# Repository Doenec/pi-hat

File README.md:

# pi-hat
collection of different shields to be stacked in raspberry pi

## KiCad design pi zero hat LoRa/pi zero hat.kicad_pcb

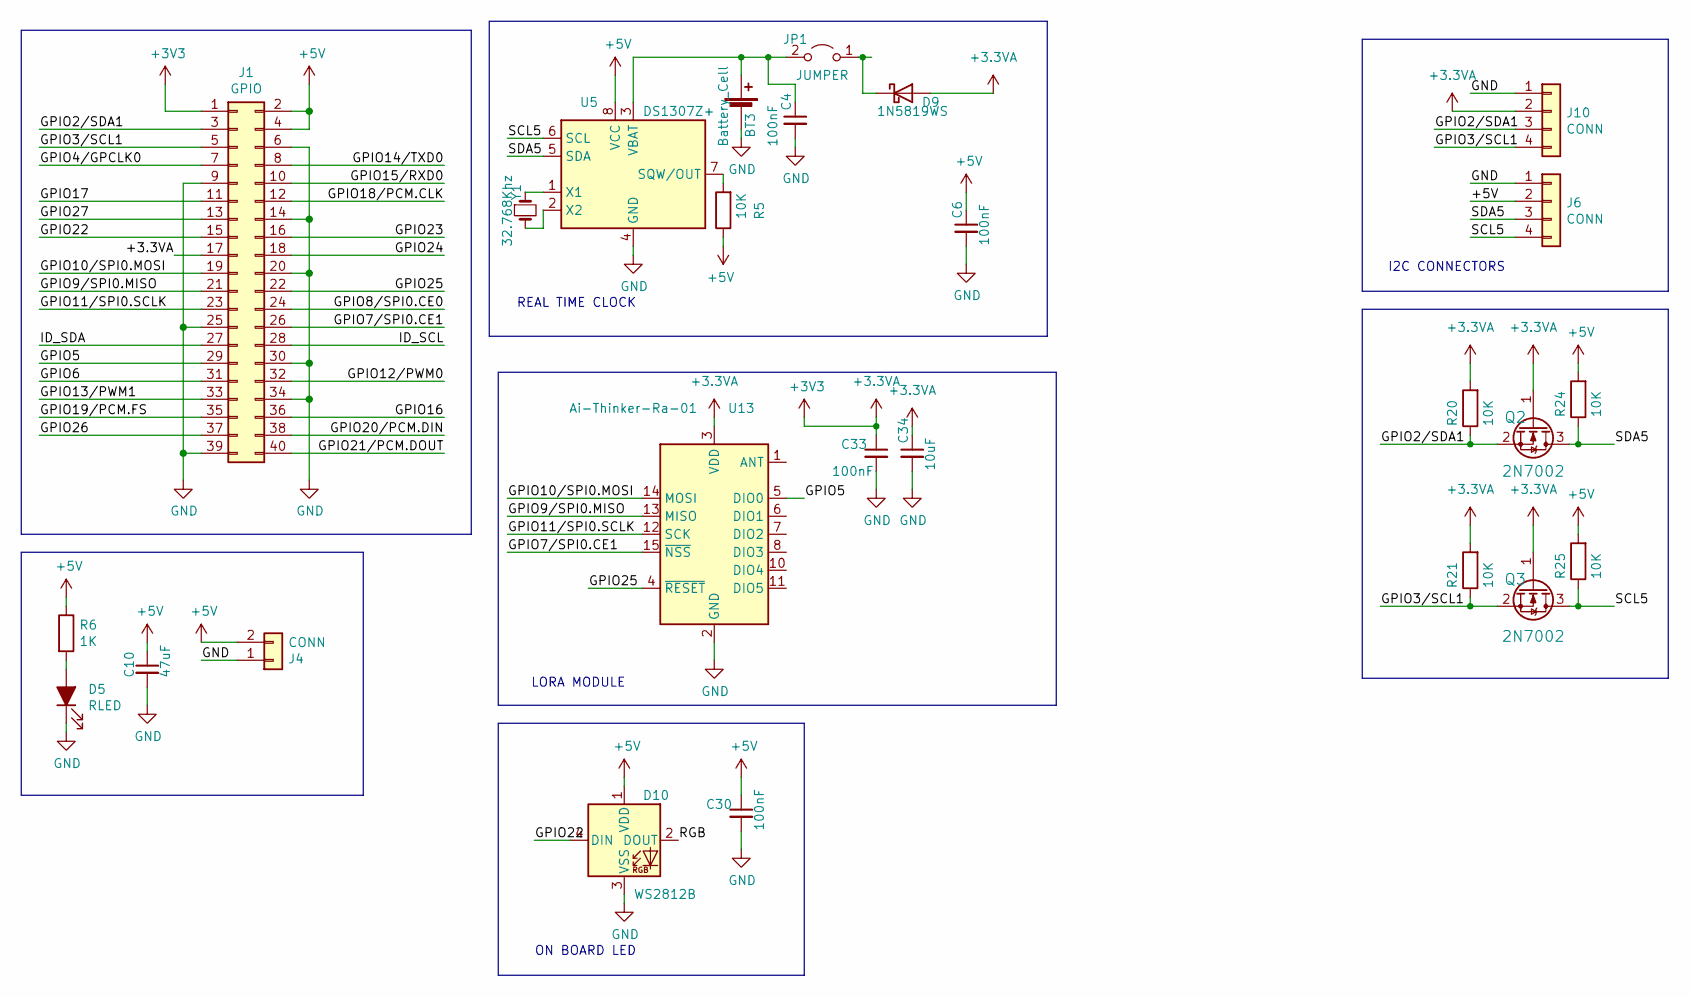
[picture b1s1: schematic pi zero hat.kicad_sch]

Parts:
BT3: Battery_Cell; cr1220-2; MPN CR1220-2; LCSC-PN C70381
C4, C6, C30, C33: 100nF; C_0402_1005Metric; MPN CL05B104KO5NNNC; LCSC-PN C1525
C10: 47uF; C_1206_3216Metric; MPN CL31A476MPHNNNE; LCSC-PN C96123
C34: 10uF; C_0402_1005Metric; MPN CL05A106MQ5NUNC; LCSC-PN C15525
D5: RLED; LED_0603_1608Metric; MPN KT-0603R; LCSC-PN C2286
D9: 1N5819WS; D_SOD-323; MPN 1N5819WS; LCSC-PN C191023
D10: WS2812B; LED_WS2812B_PLCC4_5.0x5.0mm_P3.2mm; MPN WS2812E-V5; LCSC-PN C2920042
J1: GPIO; PinSocket_2x20_P2.54mm_Vertical
J4: CONN; JST_PH_B2B-PH-K_1x02_P2.00mm_Vertical
J6, J10: CONN; PinHeader_1x04_P2.54mm_Vertical
JP1: JUMPER; SolderJumper-2_P1.3mm_Open_RoundedPad1.0x1.5mm
Q2, Q3: 2N7002; SOT-23; MPN 2N7002; LCSC-PN C8545
R5, R20, R21, R24, R25: 10K; R_0402_1005Metric; MPN 0402WGF1002TCE; LCSC-PN C25744
R6: 1K; R_0603_1608Metric; MPN 0603WAF1001T5E; LCSC-PN C21190
U5: DS1307Z+; SOIC-8_3.9x4.9mm_P1.27mm; MPN DS1307Z+T&R; LCSC-PN C9868
U13: Ai-Thinker-Ra-01; Ai-Thinker-Ra-01-LoRa
Y1: 32.768Khz; Crystal_SMD_G8-2Pin_3.2x1.5mm; MPN Q13FC1350000400; LCSC-PN C32346

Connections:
+3.3VA: C33.1, C34.1, D9.2 (A), J1.1, J1.17, J10.2, Q2.1 (G), Q3.1 (G), R20.2, R21.2, U13.3 (VDD)
+5V: C6.1, C10.1, C30.1, D10.1 (VDD), J1.2, J1.4, J4.2, J6.2, R5.1, R6.1, R24.2, R25.2, U5.8 (VCC)
/GPIO2/SDA1: J1.3, J10.3, Q2.2 (S), R20.1
/GPIO3/SCL1: J1.5, J10.4, Q3.2 (S), R21.1
/GPIO4/GPCLK0: J1.7
/GPIO5: J1.29, U13.5 (DIO0)
/GPIO6: J1.31
/GPIO7/SPI0.CE1: J1.26, U13.15 (~NSS)
/GPIO8/SPI0.CE0: J1.24
/GPIO9/SPI0.MISO: J1.21, U13.13 (MISO)
/GPIO10/SPI0.MOSI: J1.19, U13.14 (MOSI)
/GPIO11/SPI0.SCLK: J1.23, U13.12 (SCK)
/GPIO12/PWM0: J1.32
/GPIO13/PWM1: J1.33
/GPIO14/TXD0: J1.8
/GPIO15/RXD0: J1.10
/GPIO16: J1.36
/GPIO17: J1.11
/GPIO18/PCM.CLK: J1.12
/GPIO19/PCM.FS: J1.35
/GPIO20/PCM.DIN: J1.38
/GPIO21/PCM.DOUT: J1.40
/GPIO22: D10.4 (DIN), J1.15
/GPIO23: J1.16
/GPIO24: J1.18
/GPIO25: J1.22, U13.4 (~RESET)
/GPIO26: J1.37
/GPIO27: J1.13
/ID_SCL: J1.28
/ID_SDA: J1.27
/RGB: D10.2 (DOUT)
/SCL5: J6.4, Q3.3 (D), R25.1, U5.6 (SCL)
/SDA5: J6.3, Q2.3 (D), R24.1, U5.5 (SDA)
GND: BT3.2 (-), C4.2, C6.2, C10.2, C30.2, C33.2, C34.2, D5.1 (K), D10.3 (VSS), J1.6, J1.9, J1.14, J1.20, J1.25, J1.30, J1.34, J1.39, J4.1, J6.1, J10.1, U5.4 (GND), U13.2 (GND), U13.9 (GND), U13.16 (GND)
unnamed: BT3.1 (+), C4.1, JP1.2 (B), U5.3 (VBAT)
unnamed: D5.2 (A), R6.2
unnamed: D9.1 (K), JP1.1 (A)
unnamed: R5.2, U5.7 (SQW/OUT)
unnamed: U5.1 (X1), Y1.1
unnamed: U5.2 (X2), Y1.2

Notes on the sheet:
I2C CONNECTORS
ON BOARD LED
LORA MODULE
REAL TIME CLOCK

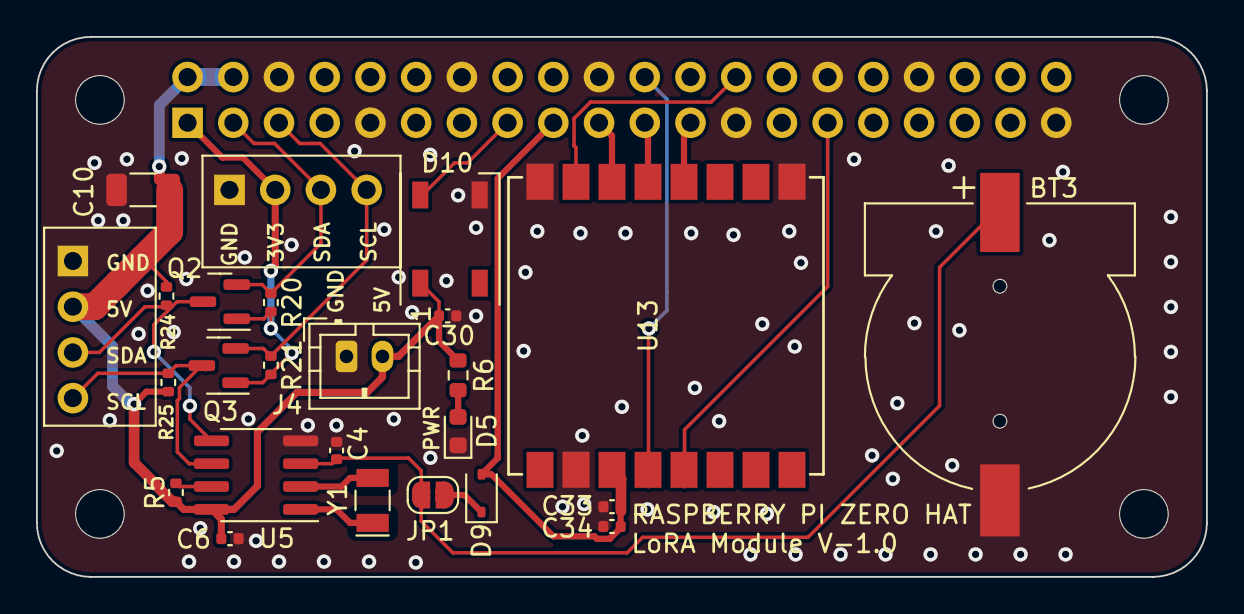
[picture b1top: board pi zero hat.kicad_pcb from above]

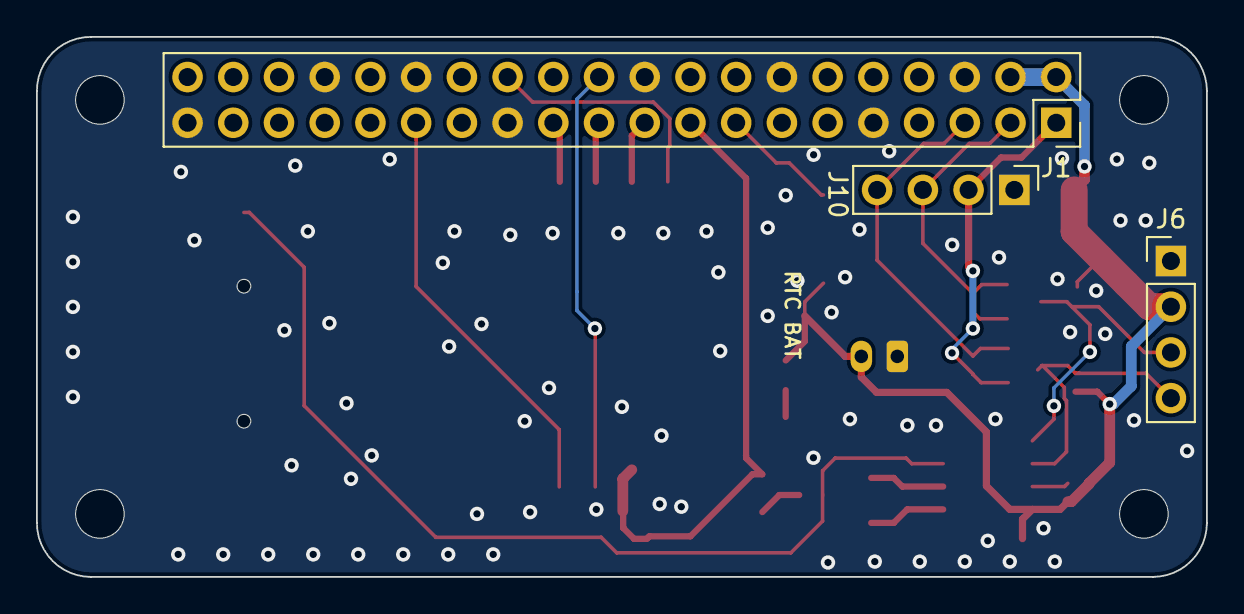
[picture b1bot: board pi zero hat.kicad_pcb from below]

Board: 2 copper layers, 65.0 x 30.0 mm, 30 parts (3 on the bottom side), 20 nets.

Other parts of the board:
MH1, MH2, MH5, MH6: MountingHole_2.7mm_M2.5

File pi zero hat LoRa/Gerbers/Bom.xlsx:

Designator | Comment | Footprint | lcsc part # | Part number | Manufacturer | Qty
J1 | GPIO | Connector_PinSocket_2.54mm:PinSocket_2x20_P2.54mm_Vertical |  |  |  | 1
J4 | CONN | Connector_JST:JST_PH_B2B-PH-K_1x02_P2.00mm_Vertical |  |  |  | 1
J6 | CONN | Connector_PinHeader_2.54mm:PinHeader_1x04_P2.54mm_Vertical |  |  |  | 1
J10 | CONN | Connector_PinHeader_2.54mm:PinHeader_1x04_P2.54mm_Vertical |  |  |  | 1
JP1 | JUMPER | Jumper:SolderJumper-2_P1.3mm_Open_RoundedPad1.0x1.5mm |  |  |  | 1
U13 | Ai-Thinker-Ra-01 | RF_Module:Ai-Thinker-Ra-01-LoRa |  |  |  | 1
R5 | 10K | Resistor_SMD:R_0402_1005Metric | C25744 | 0402WGF1002TCE | Uniroyal Elec | 1
R20 | 10K | Resistor_SMD:R_0402_1005Metric | C25744 | 0402WGF1002TCE | Uniroyal Elec | 1
R21 | 10K | Resistor_SMD:R_0402_1005Metric | C25744 | 0402WGF1002TCE | Uniroyal Elec | 1
R24 | 10K | Resistor_SMD:R_0402_1005Metric | C25744 | 0402WGF1002TCE | Uniroyal Elec | 1
R25 | 10K | Resistor_SMD:R_0402_1005Metric | C25744 | 0402WGF1002TCE | Uniroyal Elec | 1
R6 | 1K | Resistor_SMD:R_0603_1608Metric | C21190 | 0603WAF1001T5E | UNI-ROYAL(Uniroyal Elec) | 1
D9 | 1N5819WS | Diode_SMD:D_SOD-323 | C191023 | 1N5819WS | Guangdong Hottech | 1
Q2 | 2N7002 | Package_TO_SOT_SMD:SOT-23 | C8545 | 2N7002 | ON Semiconductor | 1
Q3 | 2N7002 | Package_TO_SOT_SMD:SOT-23 | C8545 | 2N7002 | ON Semiconductor | 1
C34 | 10uF | Capacitor_SMD:C_0402_1005Metric | C15525 | CL05A106MQ5NUNC | Samsung Electro-Mechanics | 1
C4 | 100nF | Capacitor_SMD:C_0402_1005Metric | C1525 | CL05B104KO5NNNC | Samsung Electro-Mechanics | 1
C6 | 100nF | Capacitor_SMD:C_0402_1005Metric | C1525 | CL05B104KO5NNNC | Samsung Electro-Mechanics | 1
C30 | 100nF | Capacitor_SMD:C_0402_1005Metric | C1525 | CL05B104KO5NNNC | Samsung Electro-Mechanics | 1
C33 | 100nF | Capacitor_SMD:C_0402_1005Metric | C1525 | CL05B104KO5NNNC | Samsung Electro-Mechanics | 1
C10 | 47uF | Capacitor_SMD:C_1206_3216Metric | C96123 | CL31A476MPHNNNE | Samsung Electro-Mechanics | 1
BT3 | Battery_Cell | nodemcu:cr1220-2 | C70381 | CR1220-2 | Q&J | 1
U5 | DS1307Z+ | Package_SO:SOIC-8_3.9x4.9mm_P1.27mm | C9868 | DS1307Z+T&R | Maxim Integrated | 1
D5 | RLED | LED_SMD:LED_0603_1608Metric | C2286 | KT-0603R | Hubei KENTO Elec | 1
Y1 | 32.768Khz | Crystal:Crystal_SMD_G8-2Pin_3.2x1.5mm | C32346 | Q13FC1350000400 | Seiko Epson | 1
D10 | WS2812B | LED_SMD:LED_WS2812B_PLCC4_5.0x5.0mm_P3.2mm | C2920042 | WS2812E-V5 | Worldsemi | 1

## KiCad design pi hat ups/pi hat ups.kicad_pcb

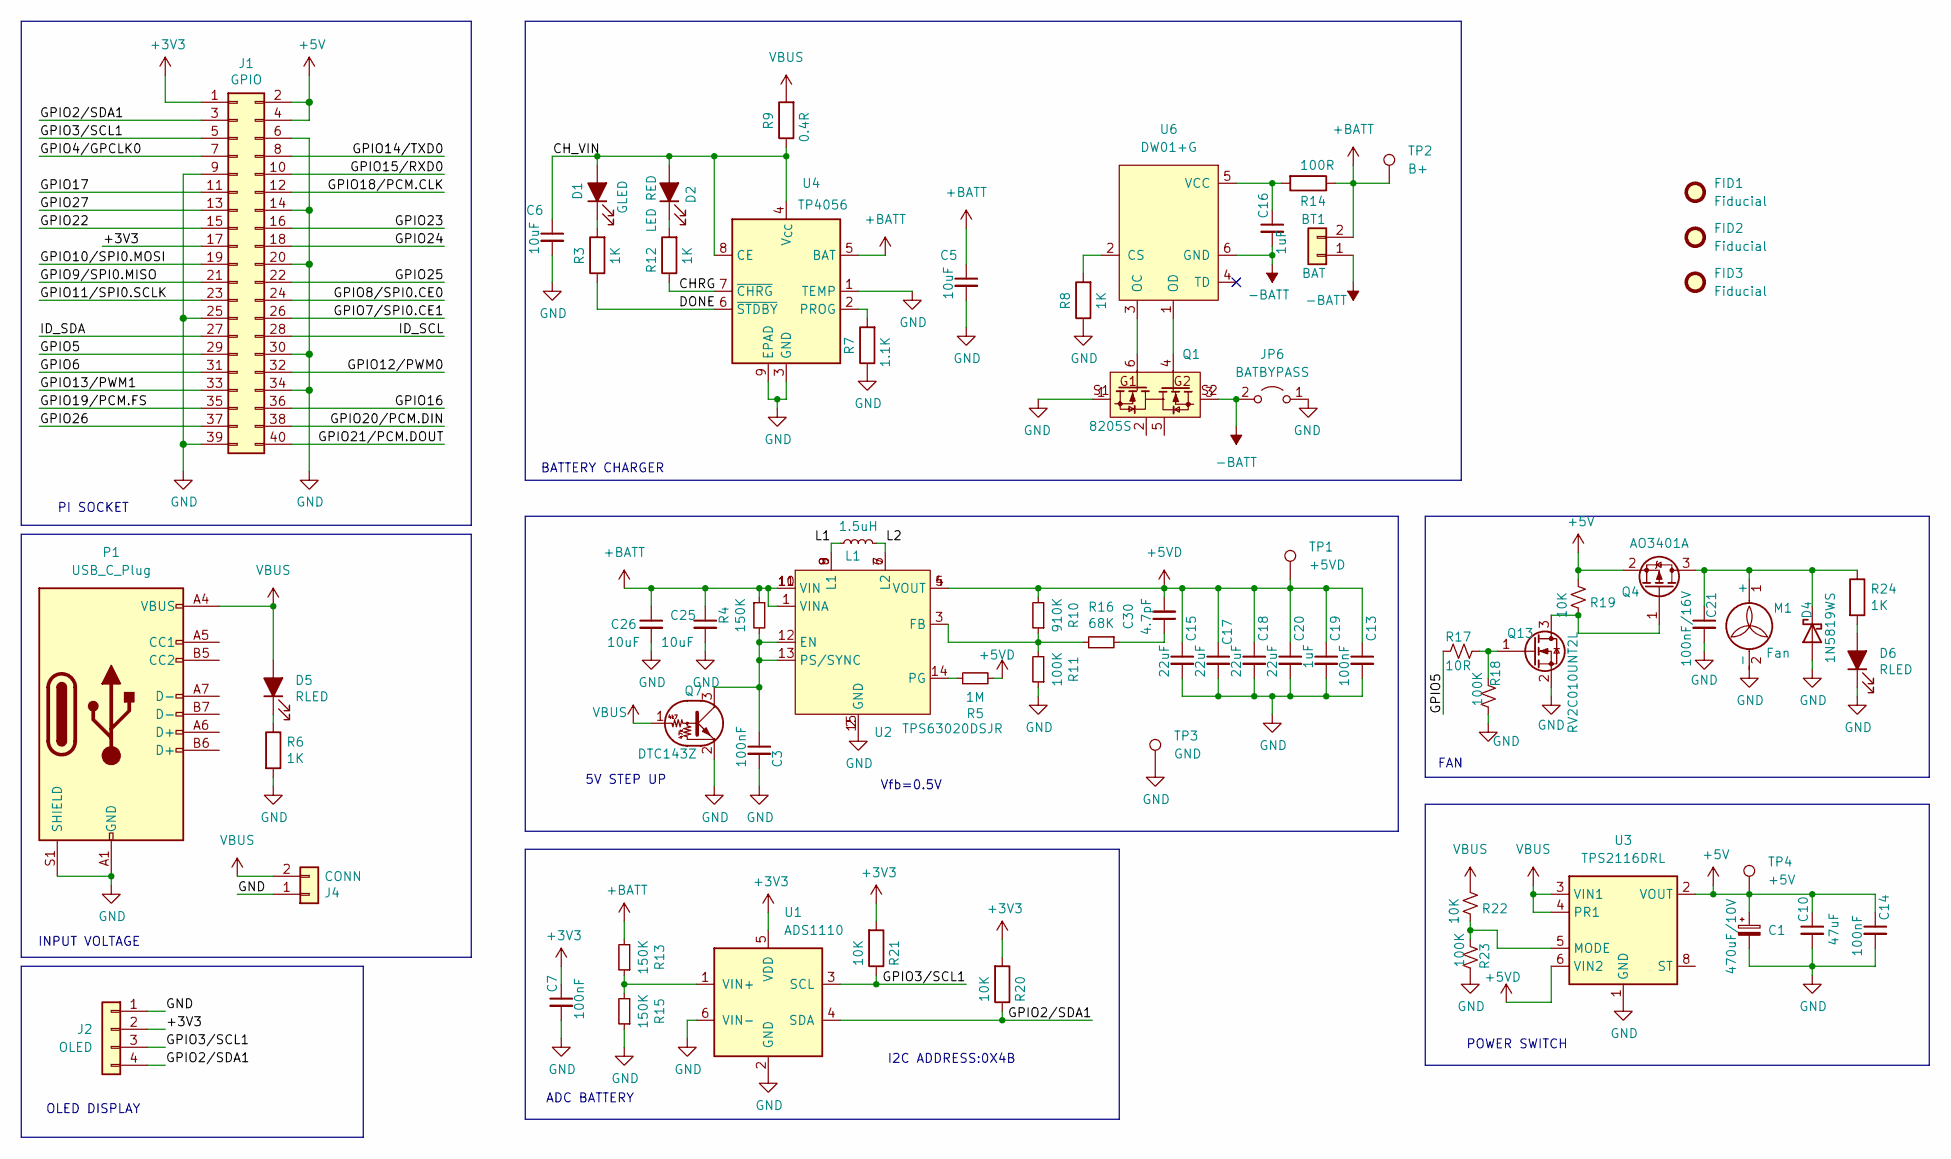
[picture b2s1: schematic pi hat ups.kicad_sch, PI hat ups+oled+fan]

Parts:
BT1: BAT; JST_PH_B2B-PH-K_1x02_P2.00mm_Vertical; MPN B2B-PH-K-S(LF)(SN); LCSC-PN C131337
C1: 470uF/10V; CP_Elec_6.3x7.7; MPN RVT470UF10V67RV0159; LCSC-PN C2858856
C3: 100nF; C_0402_1005Metric; MPN CL05B104KO5NNNC; Digi-Key_PN 490-14514-1-ND
C5, C6, C25, C26: 10uF; C_0402_1005Metric; MPN CL05A106MQ5NUNC; LCSC-PN C15525
C7, C13, C14: 100nF; C_0402_1005Metric; MPN CL05B104KO5NNNC; LCSC-PN C1525
C10: 47uF; C_1206_3216Metric; MPN CL31A476MPHNNNE; LCSC-PN C96123
C15, C17, C18, C20: 22uF; C_0603_1608Metric; MPN CL10A226MP8NUNE; LCSC-PN C86295
C16, C19: 1uF; C_0402_1005Metric; MPN CL05A105KA5NQNC; LCSC-PN C52923
C21: 100nF/16V; C_0402_1005Metric; MPN GCM155R71C104KA55J; Digi-Key_PN 490-8020-1-ND
C30: 4.7pF; C_0402_1005Metric; MPN 0402CG4R7C500NT; LCSC-PN C1569
D1: GLED; LED_0603_1608Metric; MPN 19-217/GHC-YR1S2/3T; LCSC-PN C72043
D2: LED RED; LED_0603_1608Metric; MPN KT-0603R; LCSC-PN C2286
D4: 1N5819WS; D_SOD-323; MPN 1N5819WS; Digi-Key_PN 5399-1N5819WSCT-ND
D5, D6: RLED; LED_0603_1608Metric; MPN KT-0603R; LCSC-PN C2286
FID1, FID2, FID3: Fiducial; Fiducial_0.5mm_Mask1mm
J1: GPIO; PinSocket_2x20_P2.54mm_Vertical
J2: OLED; OLED_I2C_091
J4: CONN; PinHeader_1x02_P2.54mm_Vertical
JP6: BATBYPASS; SolderJumper-2_P1.3mm_Open_RoundedPad1.0x1.5mm
L1: 1.5uH; L_Sunlord_SWPA4020S; MPN XFL4020-152MEC; LCSC-PN C3033018
M1: Fan; PinHeader_1x02_P2.54mm_Vertical
P1: USB_C_Plug; USB_C_Receptacle_HRO_TYPE-C-31-M-12; MPN TYPE-C-31-M-12; LCSC-PN C165948
Q1: 8205S; SOT-23-6; MPN TPM8205ATS6; LCSC-PN C2827645
Q4: AO3401A; SOT-23; MPN AO3401A; Digi-Key_PN 785-1001-1-ND
Q7: DTC143Z; SOT-23; MPN DTC143ZCA; LCSC-PN C15236
Q13: RV2C010UNT2L; Diodes_DFN1006-3; MPN RV2C010UNT2L; Digi-Key_PN RV2C010UNT2LCT-ND
R3, R8, R12: 1K; R_0402_1005Metric; MPN 0402WGF1001TCE; LCSC-PN C11702
R4, R13, R15: 150K; R_0402_1005Metric; MPN 0402WGF1503TCE; LCSC-PN C25755
R5: 1M; R_0402_1005Metric; MPN 0402WGF1004TCE; LCSC-PN C26083
R6, R24: 1K; R_0603_1608Metric; MPN 0603WAF1001T5E; LCSC-PN C21190
R7: 1.1K; R_0603_1608Metric; MPN 0603WAF1101T5E; LCSC-PN C22764
R9: 0.4R; R_1206_3216Metric; MPN 1206W4F400LT5E; LCSC-PN C247521
R10: 910K; R_0402_1005Metric; MPN FRC0402F9103TS; LCSC-PN C2909391
R11: 100K; R_0402_1005Metric; MPN 0402WGF1003TCE; LCSC-PN C25741
R14: 100R; R_0402_1005Metric; MPN 0402WGF1000TCE; LCSC-PN C25076
R16: 68K; R_0402_1005Metric; MPN 0402WGF6802TCE; LCSC-PN C36871
R17: 10R; R_0402_1005Metric; MPN ERJ2RKF10R0X; Digi-Key_PN P10.0LCT-ND
R18, R23: 100K; R_0402_1005Metric; MPN 0402WGF1003TCE; Digi-Key_PN P100KLCT-ND
R19, R22: 10K; R_0402_1005Metric; MPN 0402WGF1002TCE; Digi-Key_PN RMCF0402FT10K0DKR-ND
R20, R21: 10K; R_0402_1005Metric; MPN 0402WGF1002TCE; LCSC-PN C25744
TP1: +5VD; TestPoint_Pad_D1.0mm
TP2: B+; TestPoint_Pad_D1.0mm
TP3: GND; TestPoint_Pad_D1.0mm
TP4: +5V; TestPoint_Pad_D1.0mm
U1: ADS1110; SOT-23-6; MPN ADS1110A0IDBVR; LCSC-PN C16598
U2: TPS63020DSJR; VSON-14-1EP_3x4.45mm_P0.65mm_EP1.6x4.2mm_ThermalVias; MPN TPS63020DSJR; LCSC-PN C15483
U3: TPS2116DRL; SOT-583-8; MPN TPS2116DRLR; LCSC-PN C3235557
U4: TP4056; SOIC-8-1EP_3.9x4.9mm_P1.27mm_EP2.41x3.3mm_ThermalVias; MPN TP4056-42-ESOP8; LCSC-PN C16581
U6: DW01+G; SOT-23-6; MPN DW01; LCSC-PN C181096

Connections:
+3V3: C7.1, J1.1, J1.17, J2.2, R20.2, R21.2, U1.5 (VDD)
+5V: C1.1, C10.1, C14.1, J1.2, J1.4, Q4.2 (S), R19.1, TP4.1, U3.2 (VOUT), U3.7 (VOUT)
+5VD: C13.1, C15.1, C17.1, C18.1, C19.1, C20.1, C30.2, R5.2, R10.2, TP1.1, U2.4 (VOUT), U2.5 (VOUT), U3.6 (VIN2)
+BATT: BT1.2, C5.1, C25.1, C26.1, R4.1, R13.2, R14.1, TP2.1, U2.1 (VINA), U2.10 (VIN), U2.11 (VIN), U4.5 (BAT)
-BATT: BT1.1, C16.2, JP6.2 (B), Q1.3 (S2), U6.6 (GND)
/CHRG: R12.1, U4.7 (~CHRG)
/CH_VIN: C6.1, D1.2 (A), D2.2 (A), R9.1, U4.4 (V_{CC}), U4.8 (CE)
/DONE: R3.1, U4.6 (~STDBY)
/GPIO2/SDA1: J1.3, J2.4, R20.1, U1.4 (SDA)
/GPIO3/SCL1: J1.5, J2.3, R21.1, U1.3 (SCL)
/GPIO4/GPCLK0: J1.7
/GPIO5: J1.29, R17.1
/GPIO6: J1.31
/GPIO7/SPI0.CE1: J1.26
/GPIO8/SPI0.CE0: J1.24
/GPIO9/SPI0.MISO: J1.21
/GPIO10/SPI0.MOSI: J1.19
/GPIO11/SPI0.SCLK: J1.23
/GPIO12/PWM0: J1.32
/GPIO13/PWM1: J1.33
/GPIO14/TXD0: J1.8
/GPIO15/RXD0: J1.10
/GPIO16: J1.36
/GPIO17: J1.11
/GPIO18/PCM.CLK: J1.12
/GPIO19/PCM.FS: J1.35
/GPIO20/PCM.DIN: J1.38
/GPIO21/PCM.DOUT: J1.40
/GPIO22: J1.15
/GPIO23: J1.16
/GPIO24: J1.18
/GPIO25: J1.22
/GPIO26: J1.37
/GPIO27: J1.13
/ID_SCL: J1.28
/ID_SDA: J1.27
/L1: L1.1, U2.8 (L1), U2.9 (L1)
/L2: L1.2, U2.6 (L2), U2.7 (L2)
GND: C1.2, C3.2, C5.2, C6.2, C7.2, C10.2, C13.2, C14.2, C15.2, C17.2, C18.2, C19.2, C20.2, C21.2, C25.2, C26.2, D4.2 (A), D6.1 (K), J1.6, J1.9, J1.14, J1.20, J1.25, J1.30, J1.34, J1.39, J2.1, J4.1, JP6.1 (A), M1.2 (-), P1.A1 (GND), P1.A12 (GND), P1.B1 (GND), P1.B12 (GND), P1.S1 (SHIELD), Q1.1 (S), Q7.2 (E), Q13.2 (S), R6.2, R7.1, R8.1, R11.1, R15.1, R18.2, R23.2, TP3.1, U1.2 (GND), U1.6 (VIN-), U2.2 (GND), U2.15 (GND), U3.1 (GND), U4.1 (TEMP), U4.3 (GND), U4.9 (EPAD)
unnamed: C30.1, R16.1
unnamed: D1.1 (K), R3.2
unnamed: D2.1 (K), R12.2
unnamed: C21.1, D4.1 (K), M1.1 (+), Q4.3 (D), R24.1
unnamed: D5.1 (K), R6.1
unnamed: D6.2 (A), R24.2
unnamed: Q1.6 (G1), U6.3 (OC)
unnamed: Q1.4 (G2), U6.1 (OD)
unnamed: C3.1, Q7.3 (C), R4.2, U2.12 (EN), U2.13 (PS/SYNC)
unnamed: Q4.1 (G), Q13.3 (D), R19.2
unnamed: Q13.1 (G), R17.2, R18.1
unnamed: R13.1, R15.2, U1.1 (VIN+)
unnamed: R10.1, R11.2, R16.2, U2.3 (FB)
unnamed: R5.1, U2.14 (PG)
unnamed: R22.2, R23.1, U3.5 (MODE)
unnamed: R7.2, U4.2 (PROG)
unnamed: R8.2, U6.2 (CS)
unnamed: C16.1, R14.2, U6.5 (VCC)
VBUS: D5.2 (A), J4.2, P1.A4 (VBUS), P1.A9 (VBUS), P1.B4 (VBUS), P1.B9 (VBUS), Q7.1 (B), R9.2, R22.1, U3.3 (VIN1), U3.4 (PR1)

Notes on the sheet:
I2C ADDRESS:0X4B
Vfb=0.5V
ADC BATTERY
POWER SWITCH
FAN
PI SOCKET
5V STEP UP
BATTERY CHARGER
INPUT VOLTAGE
OLED DISPLAY

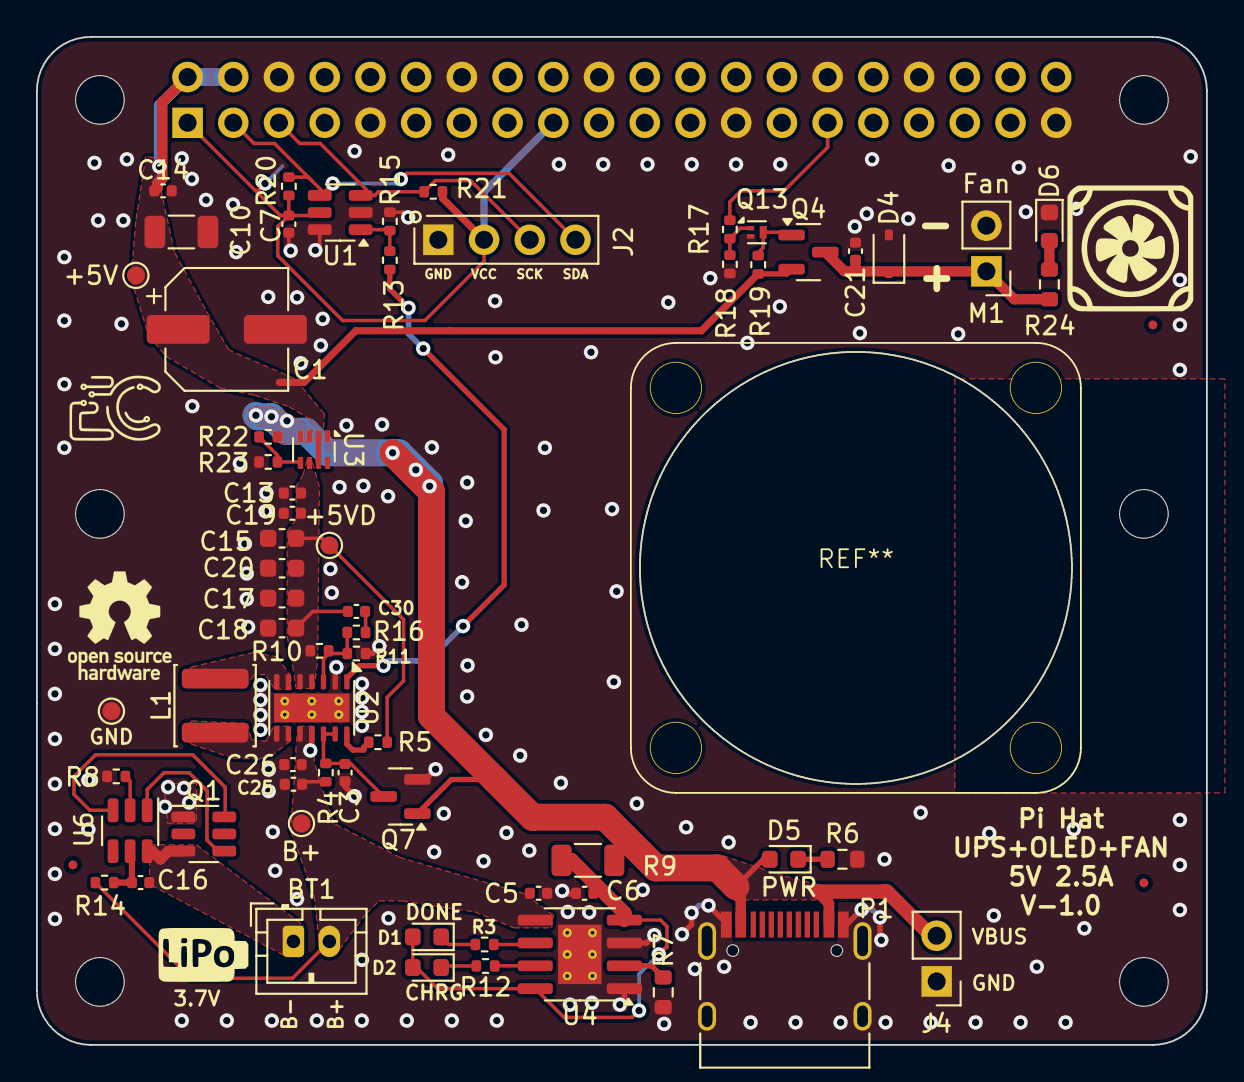
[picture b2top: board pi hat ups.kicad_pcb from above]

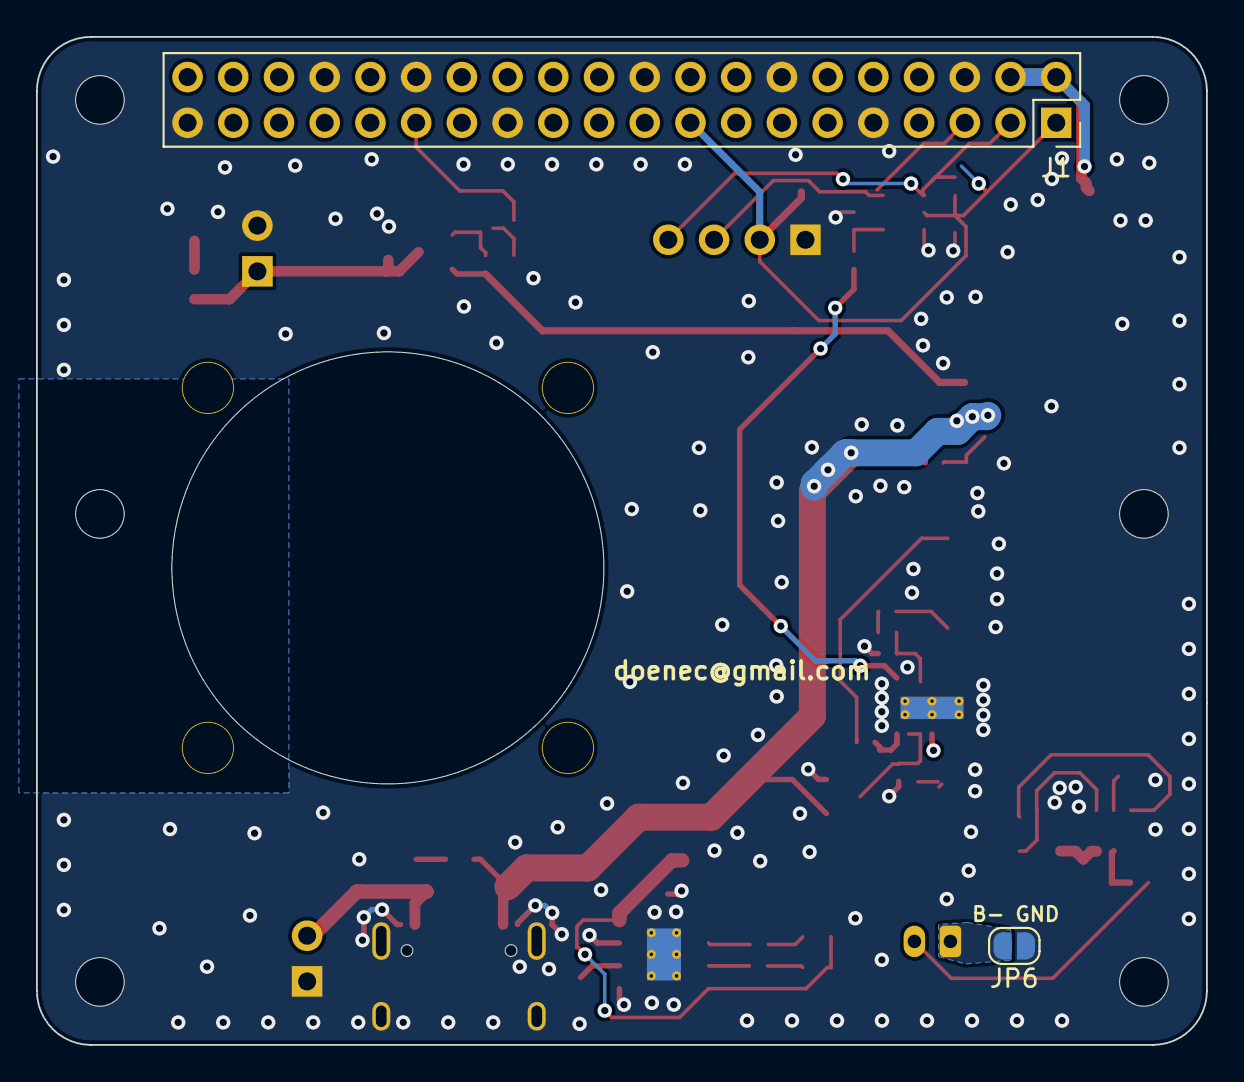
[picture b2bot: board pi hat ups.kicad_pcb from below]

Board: 4 copper layers, 65.0 x 56.0 mm, 75 parts (2 on the bottom side), 33 nets.

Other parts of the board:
MH1, MH2, MH3, MH4, MH5, MH6: MountingHole_2.7mm_M2.5

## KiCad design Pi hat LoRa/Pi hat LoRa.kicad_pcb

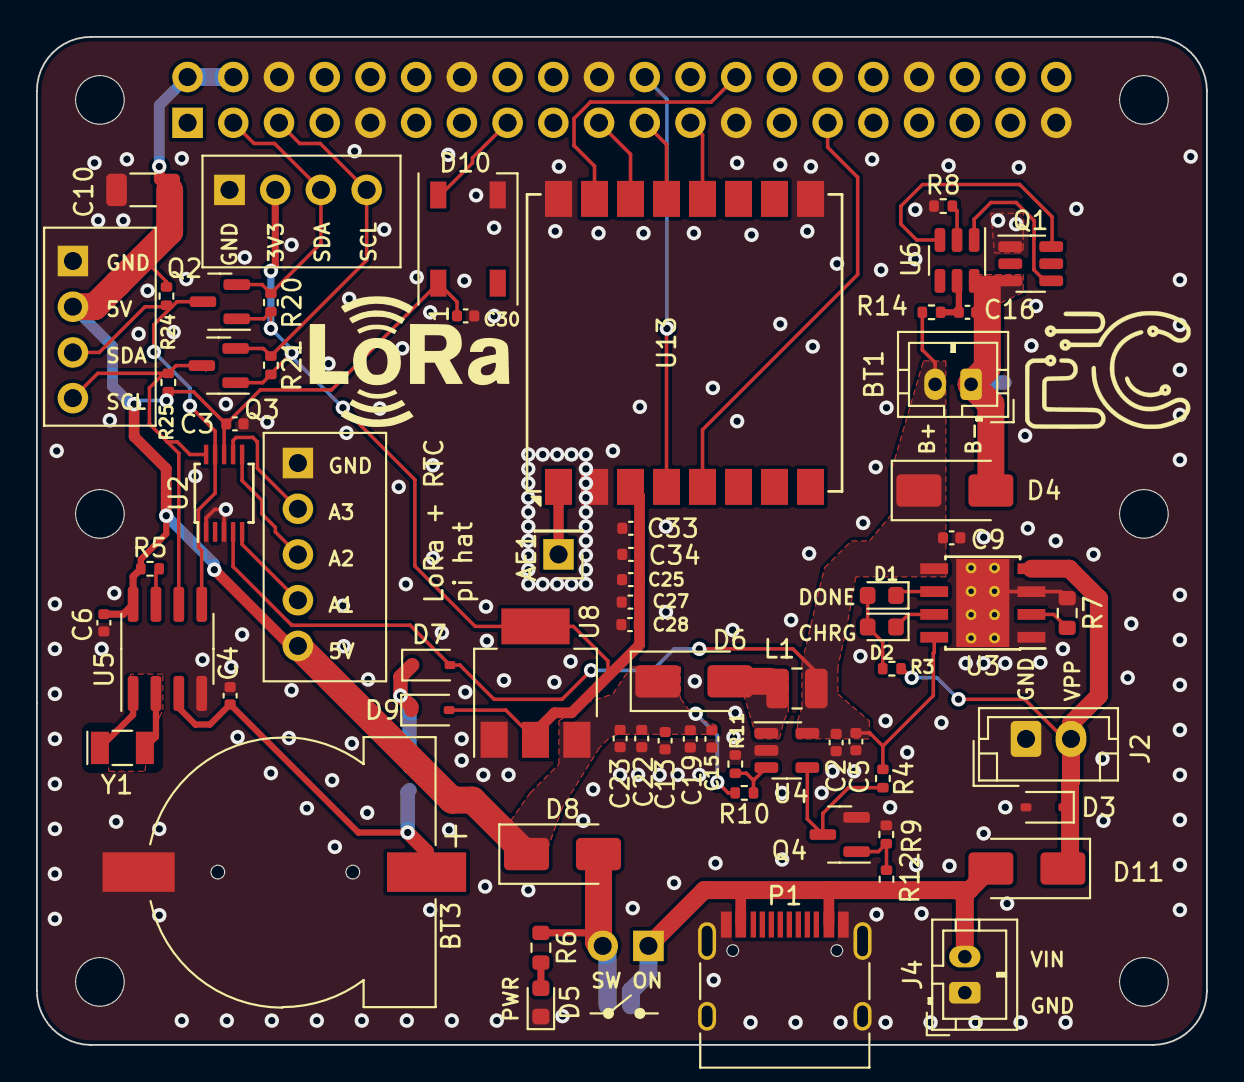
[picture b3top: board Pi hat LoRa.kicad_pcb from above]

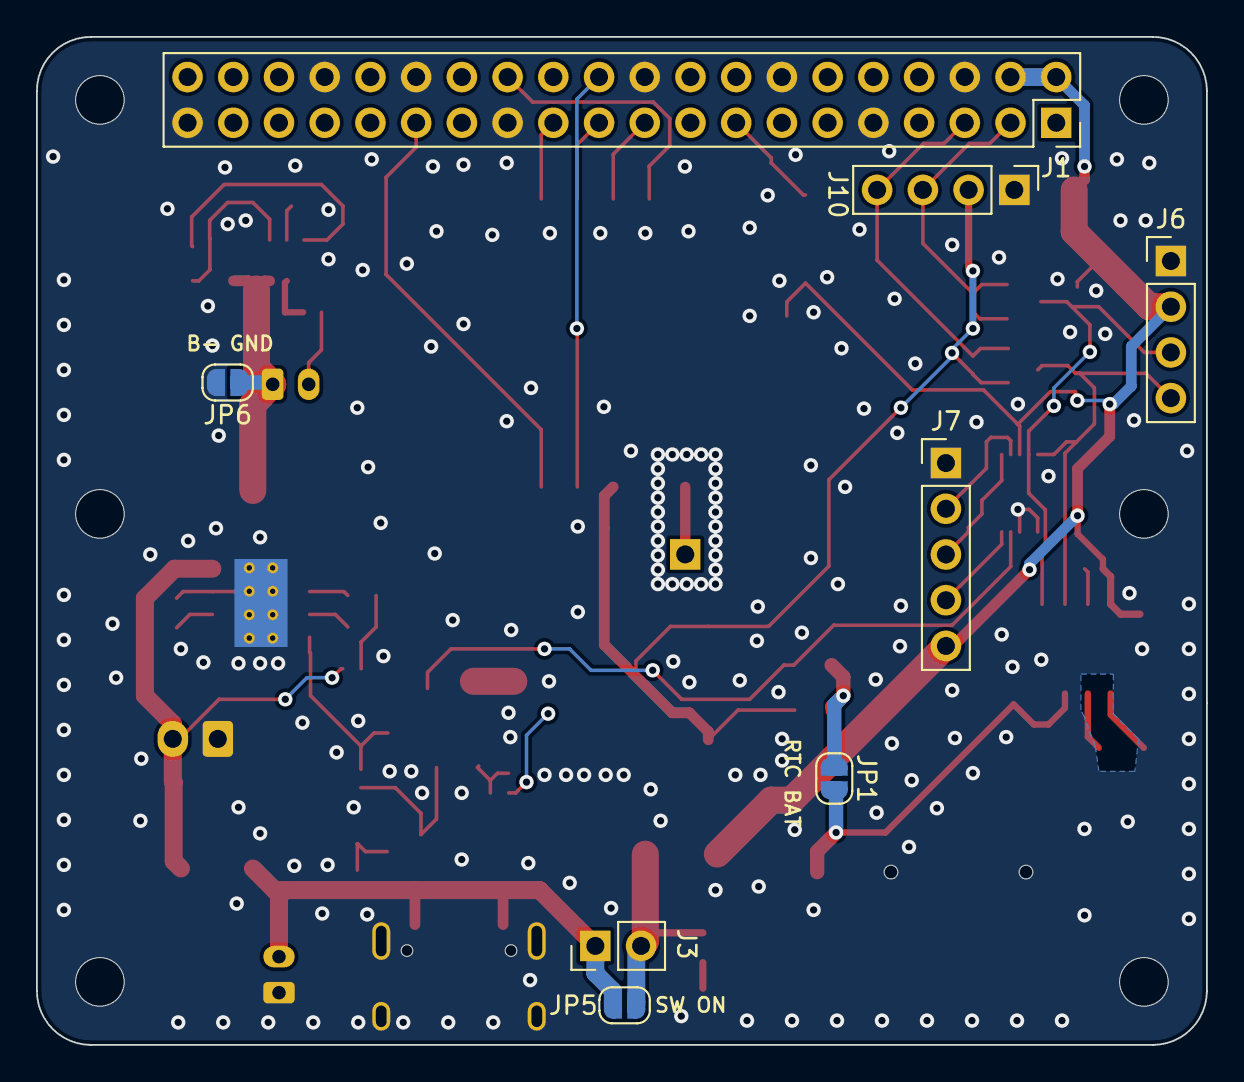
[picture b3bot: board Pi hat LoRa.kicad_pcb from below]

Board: 2 copper layers, 65.0 x 56.0 mm, 78 parts (8 on the bottom side), 41 nets.

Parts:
AE1: Antenna; PinHeader_1x01_P2.54mm_Vertical
BT1: BAT; JST_PH_B2B-PH-K_1x02_P2.00mm_Vertical
BT3: Battery_Cell; cr1220-2
C2, C9, C16, C19, C27: 1uF; C_0402_1005Metric
C3, C4, C6, C13, C23, C28, C30, C33: 100nF; C_0402_1005Metric
C5, C15, C22, C25, C34: 10uF; C_0402_1005Metric
C10: 47uF; C_1206_3216Metric
D1: GLED; LED_0603_1608Metric
D2: LED RED; LED_0603_1608Metric
D3, D7, D9: 1N5819WS; D_SOD-323
D4, D8, D11: SS34; D_SMA
D5: RLED; LED_0603_1608Metric
D6: SS210; D_SMA
D10: WS2812B; LED_WS2812B_PLCC4_5.0x5.0mm_P3.2mm
J1: GPIO; PinSocket_2x20_P2.54mm_Vertical
J2: CONN; JST_EH_B2B-EH-A_1x02_P2.50mm_Vertical
J3: CONN; PinHeader_1x02_P2.54mm_Vertical
J4: CONN; JST_PH_B2B-PH-K_1x02_P2.00mm_Vertical
J6, J10: CONN; PinHeader_1x04_P2.54mm_Vertical
J7: AIN; PinHeader_1x05_P2.54mm_Vertical
JP1, JP5: JUMPER; SolderJumper-2_P1.3mm_Open_RoundedPad1.0x1.5mm
JP6: BATBYPASS; SolderJumper-2_P1.3mm_Open_RoundedPad1.0x1.5mm
L1: 4.7uH; L_1008_2520Metric
MH1, MH2, MH3, MH4, MH5, MH6: MountingHole_2.7mm_M2.5
P1: USB_C_Plug; USB_C_Receptacle_HRO_TYPE-C-31-M-12
Q1: 8205A; SOT-23-6
Q2, Q3: 2N7002; SOT-23
Q4: MMBT3904; SOT-23
R3, R8, R12: 1K; R_0402_1005Metric
R4, R10: 150K; R_0402_1005Metric
R5, R9, R20, R21, R24, R25: 10K; R_0402_1005Metric
R6: 1K; R_0603_1608Metric
R7: 1.1K; R_0603_1608Metric
R11: 47K; R_0402_1005Metric
R14: 100R; R_0402_1005Metric
U2: ADS1115IDGS; TSSOP-10_3x3mm_P0.5mm
U3: CN3163; Texas_HSOP-8-1EP_3.9x4.9mm_P1.27mm_ThermalVias
U4: MT3540; SOT-23-5
U5: DS1307Z+; SOIC-8_3.9x4.9mm_P1.27mm
U6: DW01+G; SOT-23-6
U8: AMS1117-3.3; SOT-223-3_TabPin2
U13: Ai-Thinker-Ra-01; Ai-Thinker-Ra-01-LoRa
Y1: 32.768Khz; Crystal_SMD_G8-2Pin_3.2x1.5mm

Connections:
+3.3VA: C25.1, C27.1, C28.1, C33.1, C34.1, D9.2 (A), J10.2, Q2.1 (G), Q3.1 (G), R20.2, R21.2, U8.2 (VO), U13.3 (VDD)
+5V: C3.1, C6.1, C10.1, C13.1, C15.1, C19.1, C22.1, C23.1, C30.1, D6.1 (K), D8.1 (K), D10.1 (VDD), J1.2, J1.4, J6.2, J7.5, R5.1, R10.2, R24.2, R25.2, U2.8 (VDD), U5.8 (VCC), U8.3 (VI)
+BATT: BT1.2, C2.2, C5.1, C9.1, D4.1 (K), D7.2 (A), L1.1, R4.1, R14.1, U2.4 (AIN0), U3.5 (BAT), U3.8 (FB), U4.5 (IN)
-BATT: BT1.1, C16.2, D4.2 (A), JP6.1 (A), Q1.3 (S2), U6.6 (GND)
/A1: J7.4, U2.5 (AIN1)
/A2: J7.3, U2.6 (AIN2)
/A3: J7.2, U2.7 (AIN3)
/CHRG: D2.1 (K), U3.7 (~CHRG)
/DCIN: D11.2 (A), J3.1, J4.2, JP5.2 (B), P1.A4 (VBUS), P1.A9 (VBUS), P1.B4 (VBUS), P1.B9 (VBUS), R12.2
/DONE: D1.1 (K), U3.6 (~DONE)
/EN_5V: Q4.3 (C), R4.2, U4.4 (EN)
/GPIO2/SDA1: J1.3, J10.3, Q2.2 (S), R20.1
/GPIO3/SCL1: J1.5, J10.4, Q3.2 (S), R21.1
/GPIO5: J1.29, U13.5 (DIO0)
/GPIO7/SPI0.CE1: J1.26, U13.15 (~NSS)
/GPIO9/SPI0.MISO: J1.21, U13.13 (MISO)
/GPIO10/SPI0.MOSI: J1.19, U13.14 (MOSI)
/GPIO11/SPI0.SCLK: J1.23, U13.12 (SCK)
/GPIO22: D10.4 (DIN), J1.15
/GPIO25: J1.22, U13.4 (~RESET)
/SCL5: J6.4, Q3.3 (D), R25.1, U2.10 (SCL), U5.6 (SCL)
/SDA5: J6.3, Q2.3 (D), R24.1, U2.9 (SDA), U5.5 (SDA)
/STEP: D6.2 (A), L1.2, U4.1 (SW)
GND: BT3.2 (-), C2.1, C3.2, C4.2, C5.2, C6.2, C9.2, C10.2, C13.2, C15.2, C19.2, C22.2, C23.2, C25.2, C27.2, C28.2, C30.2, C33.2, C34.2, D3.2 (A), D5.1 (K), D10.3 (VSS), J1.6, J1.9, J1.14, J1.20, J1.25, J1.30, J1.34, J1.39, J2.1, J4.1, J6.1, J7.1, J10.1, JP6.2 (B), P1.A1 (GND), P1.A12 (GND), P1.B1 (GND), P1.B12 (GND), P1.S1 (SHIELD), Q1.1 (S), Q4.2 (E), R7.1, R8.1, R9.2, R11.1, U2.1 (ADDR), U2.3 (GND), U3.1 (TEMP), U3.3 (GND), U3.9 (PAD-GND), U4.2 (GND), U5.4 (GND), U8.1 (GND), U13.2 (GND), U13.9 (GND), U13.16 (GND)
unnamed: AE1.1 (A), U13.1 (ANT)
unnamed: BT3.1 (+), C4.1, JP1.2 (B), U5.3 (VBAT)
unnamed: D1.2 (A), D2.2 (A), R3.1
unnamed: D5.2 (A), R6.2
unnamed: D7.1 (K), D9.1 (K), JP1.1 (A)
unnamed: D8.2 (A), J3.2, JP5.1 (A), R6.1
unnamed: Q1.6 (G1), U6.3 (OC)
unnamed: Q1.4 (G2), U6.1 (OD)
unnamed: Q4.1 (B), R9.1, R12.1
unnamed: R7.2, U3.2 (ISET)
unnamed: R10.1, R11.2, U4.3 (FB)
unnamed: R5.2, U5.7 (SQW/OUT)
unnamed: U5.1 (X1), Y1.1
unnamed: U5.2 (X2), Y1.2
unnamed: R8.2, U6.2 (CS)
unnamed: C16.1, R14.2, U6.5 (VCC)
VPP: D3.1 (K), D11.1 (K), J2.2, R3.2, U3.4 (VIN)

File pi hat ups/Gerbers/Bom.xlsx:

Designator | Comment | Footprint | lcsc part # | Part number | Manufacturer | Qty
C3 | 100nF | Capacitor_SMD:C_0402_1005Metric | C1525 | CL05B104KO5NNNC | Samsung Electro-Mechanics | 1
C4 | 100nF | Capacitor_SMD:C_0402_1005Metric | C1525 | CL05B104KO5NNNC | Samsung Electro-Mechanics | 1
C6 | 100nF | Capacitor_SMD:C_0402_1005Metric | C1525 | CL05B104KO5NNNC | Samsung Electro-Mechanics | 1
C13 | 100nF | Capacitor_SMD:C_0402_1005Metric | C1525 | CL05B104KO5NNNC | Samsung Electro-Mechanics | 1
C23 | 100nF | Capacitor_SMD:C_0402_1005Metric | C1525 | CL05B104KO5NNNC | Samsung Electro-Mechanics | 1
C28 | 100nF | Capacitor_SMD:C_0402_1005Metric | C1525 | CL05B104KO5NNNC | Samsung Electro-Mechanics | 1
C30 | 100nF | Capacitor_SMD:C_0402_1005Metric | C1525 | CL05B104KO5NNNC | Samsung Electro-Mechanics | 1
C33 | 100nF | Capacitor_SMD:C_0402_1005Metric | C1525 | CL05B104KO5NNNC | Samsung Electro-Mechanics | 1
D2 | LED RED | LED_SMD:LED_0603_1608Metric | C2286 | KT-0603R | Hubei KENTO Elec | 1
D5 | RLED | LED_SMD:LED_0603_1608Metric | C2286 | KT-0603R | Hubei KENTO Elec | 1
U8 | AMS1117-3.3 | Package_TO_SOT_SMD:SOT-223-3_TabPin2 | C6186 | AMS1117-3.3 | Advanced Monolithic Systems | 1
Q2 | 2N7002 | Package_TO_SOT_SMD:SOT-23 | C8545 | 2N7002 | ON Semiconductor | 1
Q3 | 2N7002 | Package_TO_SOT_SMD:SOT-23 | C8545 | 2N7002 | ON Semiconductor | 1
D4 | SS34 | Diode_SMD:D_SMA | C8678 | SS34 |  | 1
D8 | SS34 | Diode_SMD:D_SMA | C8678 | SS34 |  | 1
D11 | SS34 | Diode_SMD:D_SMA | C8678 | SS34 |  | 1
U5 | DS1307Z+ | Package_SO:SOIC-8_3.9x4.9mm_P1.27mm | C9868 | DS1307Z+T&R | Maxim Integrated | 1
R3 | 1K | Resistor_SMD:R_0402_1005Metric | C11702 | 0402WGF1001TCE | Uniroyal Elec | 1
R8 | 1K | Resistor_SMD:R_0402_1005Metric | C11702 | 0402WGF1001TCE | Uniroyal Elec | 1
R12 | 1K | Resistor_SMD:R_0402_1005Metric | C11702 | 0402WGF1001TCE | Uniroyal Elec | 1
D6 | SS210 | Diode_SMD:D_SMA | C14996 | SS210 | MDD | 1
C5 | 10uF | Capacitor_SMD:C_0402_1005Metric | C15525 | CL05A106MQ5NUNC | Samsung Electro-Mechanics | 1
C15 | 10uF | Capacitor_SMD:C_0402_1005Metric | C15525 | CL05A106MQ5NUNC | Samsung Electro-Mechanics | 1
C22 | 10uF | Capacitor_SMD:C_0402_1005Metric | C15525 | CL05A106MQ5NUNC | Samsung Electro-Mechanics | 1
C25 | 10uF | Capacitor_SMD:C_0402_1005Metric | C15525 | CL05A106MQ5NUNC | Samsung Electro-Mechanics | 1
C34 | 10uF | Capacitor_SMD:C_0402_1005Metric | C15525 | CL05A106MQ5NUNC | Samsung Electro-Mechanics | 1
Q4 | MMBT3904 | Package_TO_SOT_SMD:SOT-23 | C20526 | MMBT3904 | C20526 | 1
R6 | 1K | Resistor_SMD:R_0603_1608Metric | C21190 | 0603WAF1001T5E | UNI-ROYAL(Uniroyal Elec) | 1
R7 | 1.1K | Resistor_SMD:R_0603_1608Metric | C22764 | 0603WAF1101T5E |  | 1
R14 | 100R | Resistor_SMD:R_0402_1005Metric | C25076 | 0402WGF1000TCE |  | 1
R5 | 10K | Resistor_SMD:R_0402_1005Metric | C25744 | 0402WGF1002TCE | Uniroyal Elec | 1
R9 | 10K | Resistor_SMD:R_0402_1005Metric | C25744 | 0402WGF1002TCE | Uniroyal Elec | 1
R20 | 10K | Resistor_SMD:R_0402_1005Metric | C25744 | 0402WGF1002TCE | Uniroyal Elec | 1
R21 | 10K | Resistor_SMD:R_0402_1005Metric | C25744 | 0402WGF1002TCE | Uniroyal Elec | 1
R24 | 10K | Resistor_SMD:R_0402_1005Metric | C25744 | 0402WGF1002TCE | Uniroyal Elec | 1
R25 | 10K | Resistor_SMD:R_0402_1005Metric | C25744 | 0402WGF1002TCE | Uniroyal Elec | 1
R4 | 150K | Resistor_SMD:R_0402_1005Metric | C25755 | 0402WGF1503TCE | Uniroyal Elec | 1
R10 | 150K | Resistor_SMD:R_0402_1005Metric | C25755 | 0402WGF1503TCE | Uniroyal Elec | 1
R11 | 47K | Resistor_SMD:R_0402_1005Metric | C25792 | 0402WGF4702TCE | UNI-ROYAL(Uniroyal Elec) | 1
Y1 | 32.768Khz | Crystal:Crystal_SMD_G8-2Pin_3.2x1.5mm | C32346 | Q13FC1350000400 | Seiko Epson | 1
U2 | ADS1115IDGS | Package_SO:TSSOP-10_3x3mm_P0.5mm | C37593 | ADS1115IDGSR | Texas Instruments | 1
C2 | 1uF | Capacitor_SMD:C_0402_1005Metric | C52923 | CL05A105KA5NQNC | Samsung Electro-Mechanics | 1
C9 | 1uF | Capacitor_SMD:C_0402_1005Metric | C52923 | CL05A105KA5NQNC | Samsung Electro-Mechanics | 1
C16 | 1uF | Capacitor_SMD:C_0402_1005Metric | C52923 | CL05A105KA5NQNC | Samsung Electro-Mechanics | 1
C19 | 1uF | Capacitor_SMD:C_0402_1005Metric | C52923 | CL05A105KA5NQNC | Samsung Electro-Mechanics | 1
C27 | 1uF | Capacitor_SMD:C_0402_1005Metric | C52923 | CL05A105KA5NQNC | Samsung Electro-Mechanics | 1
BT3 | Battery_Cell | nodemcu:cr1220-2 | C70381 | CR1220-2 | Q&J | 1
D1 | GLED | LED_SMD:LED_0603_1608Metric | C72043 | 19-217/GHC-YR1S2/3T | Everlight Elec | 1
C10 | 47uF | Capacitor_SMD:C_1206_3216Metric | C96123 | CL31A476MPHNNNE | Samsung Electro-Mechanics | 1
P1 | USB_C_Plug | Connector_USB:USB_C_Receptacle_HRO_TYPE-C-31-M-12 | C165948 | TYPE-C-31-M-12 | Korean Hroparts Elec | 1
U6 | DW01+G | Package_TO_SOT_SMD:SOT-23-6 | C181096 | DW01 | Guangdong Hottech | 1
U4 | MT3540 | Package_TO_SOT_SMD:SOT-23-5 | C181744 | MT3540 | XI'AN Aerosemi Tech | 1
D3 | 1N5819WS | Diode_SMD:D_SOD-323 | C191023 | 1N5819WS | Guangdong Hottech | 1
D7 | 1N5819WS | Diode_SMD:D_SOD-323 | C191023 | 1N5819WS | Guangdong Hottech | 1
D9 | 1N5819WS | Diode_SMD:D_SOD-323 | C191023 | 1N5819WS | Guangdong Hottech | 1
L1 | 4.7uH | Inductor_SMD:L_1008_2520Metric | C404806 | TFM252012ALMA4R7MTAA | TDK | 1
U3 | CN3163 | Package_SO:Texas_HSOP-8-1EP_3.9x4.9mm_P1.27mm_ThermalVias | C559031 | CN3163 | ShangHai Consonance Elec | 1
Q1 | 8205A | Package_TO_SOT_SMD:SOT-23-6 | C2827645 | TPM8205ATS6 | TECH PUBLIC | 1
D10 | WS2812B | LED_SMD:LED_WS2812B_PLCC4_5.0x5.0mm_P3.2mm | C2920042 | WS2812E-V5 | Worldsemi | 1

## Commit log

2025-06-02 files update
2025-06-10 pi hat ups.
2025-06-13 zero pi hat Lo.
